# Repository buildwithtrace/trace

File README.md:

# Trace - AI-Native PCB Design Suite

**Trace is a modified version of the KiCad EDA software, enhanced with AI-native circuit design capabilities.**

> **Important:** Trace is based on [KiCad](https://www.kicad.org/), an open-source electronics design automation suite. This is an independent fork created and maintained by the Trace team. Trace is not affiliated with, endorsed by, or supported by the KiCad project or The Linux Foundation.

For specific documentation about [building Trace](https://docs.buildwithtrace.com/build/), policies and guidelines, and source code documentation see the [Trace Documentation](https://docs.buildwithtrace.com) website.

You may also take a look into the [Wiki](https://github.com/buildwithtrace/trace/wiki) and the [contribution guide](https://docs.buildwithtrace.com/contribute/).

---

## About Trace

Trace extends KiCad's powerful PCB design tools with:
- **AI Circuit Assistant**: Natural language circuit design and modification
- **Intelligent Component Search**: AI-native part finding and suggestions  
- **Automated Routing**: Smart trace routing with AI optimization
- **Cloud Integration**: Sync designs and collaborate with your team
- **Enhanced Workflow**: Streamlined UI for modern hardware engineering

## License & Compliance

### Open Source License

Trace is released under the **GNU General Public License v3** (GPLv3), the same license as KiCad.

- **License Text**: See [LICENSE](LICENSE) file in this repository
- **Source Code**: This repository contains the complete source code for Trace
- **Full Source Archive**: Available at https://github.com/buildwithtrace/trace

As required by GPLv3, you are free to:
- Use Trace for any purpose
- Study and modify the source code
- Share copies with others
- Distribute modified versions (under GPLv3)

### Copyright & Attribution

```
Copyright (C) 2025-2026 Trace Developers (see TRACE_AUTHORS.txt)
Copyright (C) 1992-2024 KiCad Developers (see AUTHORS.txt)

Trace incorporates substantial code from the KiCad project.
KiCad is copyright its contributors and licensed under GPLv3.
```

**Modification Notice**: This software is a modified version of KiCad EDA, adapted by the Trace team starting December 2025. Original KiCad code and modifications are both licensed under GPLv3.

### Trademark Notice

**KiCad** is a registered trademark of The Linux Foundation. All rights reserved.  
**Trace** is a trademark of the Trace team.

Trace is an independent product and is not affiliated with or endorsed by the KiCad project, The Linux Foundation, or any KiCad contributors. Any bugs, issues, or support requests for Trace should be directed to the Trace team, not the KiCad project.

### Third-Party Licenses

This software includes components under various open-source licenses:
- **KiCad Libraries**: Creative Commons Attribution-ShareAlike 4.0 (CC-BY-SA 4.0)
- **Various Components**: MIT, BSD, Apache, and other permissive licenses
- See individual `LICENSE*` files in subdirectories for details

### Proprietary Components

> **Important:** The [`trace/`](trace/) directory contains Trace's proprietary AI-native design modules and is **NOT** covered by GPLv3. All files under `trace/` and its subdirectories are **All Rights Reserved** and are provided for reference only. See [`trace/LICENSE`](trace/LICENSE) for the full terms. Contact hello@buildwithtrace.com for licensing inquiries.

### No Warranty

```
THIS SOFTWARE IS PROVIDED "AS IS" WITHOUT WARRANTY OF ANY KIND, EXPRESS OR
IMPLIED, INCLUDING BUT NOT LIMITED TO THE WARRANTIES OF MERCHANTABILITY,
FITNESS FOR A PARTICULAR PURPOSE AND NONINFRINGEMENT. IN NO EVENT SHALL THE
AUTHORS OR COPYRIGHT HOLDERS BE LIABLE FOR ANY CLAIM, DAMAGES OR OTHER
LIABILITY, WHETHER IN AN ACTION OF CONTRACT, TORT OR OTHERWISE, ARISING FROM,
OUT OF OR IN CONNECTION WITH THE SOFTWARE OR THE USE OR OTHER DEALINGS IN
THE SOFTWARE.
```

See the [LICENSE](LICENSE) file for complete GPL warranty disclaimer.

---

## Building Trace from Source

### Prerequisites

- **CMake** 3.16 or later
- **C++ compiler** with C++17 support (GCC 8+, Clang 8+, MSVC 2019+)
- **Python** 3.8+ with wxPython
- **Git** for cloning the repository
- Platform-specific dependencies (see below)

### Build Instructions

#### macOS

Use our official Mac builder:
```bash
git clone https://github.com/buildwithtrace/trace-mac-builder
cd trace-mac-builder
python build.py
```

See [trace-mac-builder](https://github.com/buildwithtrace/trace-mac-builder) for detailed instructions.

#### Windows

Use our official Windows builder:
```bash
git clone https://github.com/buildwithtrace/trace-win-builder
cd trace-win-builder
# Follow instructions in repository
```

See [trace-win-builder](https://github.com/buildwithtrace/trace-win-builder) for detailed instructions.

#### Linux

```bash
# Install dependencies (Ubuntu/Debian example)
sudo apt-get update
sudo apt-get install -y cmake g++ git python3 python3-wxgtk4.0 \
    libboost-all-dev libglew-dev libcairo2-dev libcurl4-openssl-dev \
    libssl-dev libngspice0-dev libocct-*-dev swig

# Clone and build
git clone https://github.com/buildwithtrace/trace
cd trace
mkdir -p build/release
cd build/release
cmake ../.. -DCMAKE_BUILD_TYPE=Release
make -j$(nproc)
sudo make install
```

For detailed build documentation, see [Developer Documentation](https://docs.buildwithtrace.com).

---

## Files

* [AUTHORS.txt](AUTHORS.txt) - KiCad authors, contributors, document writers and translators (see [original on GitLab](https://gitlab.com/kicad/code/kicad/-/blob/master/AUTHORS.txt))
* [TRACE_AUTHORS.txt](TRACE_AUTHORS.txt) - Trace-specific contributors and developers
* [CMakeLists.txt](CMakeLists.txt) - Main CMAKE build tool script
* [copyright.h](copyright.h) - A very short copy of the GNU General Public License to be included in new source files
* [Doxyfile](Doxyfile) - Doxygen config file for Trace
* [INSTALL.txt](INSTALL.txt) - The release (binary) installation instructions
* [uncrustify.cfg](uncrustify.cfg) - Uncrustify config file for uncrustify sources formatting tool
* [_clang-format](_clang-format) - clang config file for clang-format sources formatting tool

---

## Getting Started

1. **Download**: Get the latest Trace installer from [buildwithtrace.com](https://buildwithtrace.com)
2. **Install**: Run the installer for your platform
3. **Sign In**: Create a free account to access AI features
4. **Start Designing**: Launch Trace and start a new schematic

### AI Features

Trace's AI assistant helps you design circuits faster:
- Type what you want in natural language: "Add a 555 timer circuit"
- Ask questions: "How do I add decoupling capacitors?"
- Get component suggestions: "Find a low-power MCU for battery operation"
- Auto-route your PCB with intelligent algorithms

---

## Documentation

- **User Guide**: [docs.buildwithtrace.com/docs/guides/first-pcb](https://docs.buildwithtrace.com/guides/first-pcb)
- **API Documentation**: [docs.buildwithtrace.com/docs/api](https://docs.buildwithtrace.com/api/overview)
- **Discord Community**: [Join us on Discord](https://discord.gg/UNUvQxneCr) - Get help, report bugs, discuss features, and stay updated
- **KiCad Documentation**: For core EDA features, [KiCad docs](https://docs.kicad.org/) may be helpful

---

## Project Structure

- **[3d-viewer](3d-viewer)** - Sourcecode of the 3D viewer
- **[bitmap2component](bitmap2component)** - Sourcecode of the bitmap to PCB artwork converter
- **[cmake](cmake)** - Modules for the CMAKE build tool
- **[common](common)** - Sourcecode of the common library
- **[cvpcb](cvpcb)** - Sourcecode of the CvPCB tool
- **[demos](demos)** - Some demo examples
- **[doxygen](doxygen)** - Configuration for generating pretty doxygen manual of the codebase
- **[eeschema](eeschema)** - Sourcecode of the schematic editor with AI integration
- **[gerbview](gerbview)** - Sourcecode of the gerber viewer
- **[include](include)** - Interfaces to the common library
- **[kicad](kicad)** - Sourcecode of the project manager
- **[libs](libs)** - Sourcecode of Trace utilities (geometry and others)
- **[pagelayout_editor](pagelayout_editor)** - Sourcecode of the pagelayout editor
- **[patches](patches)** - Collection of patches for external dependencies
- **[pcbnew](pcbnew)** - Sourcecode of the printed circuit board editor
- **[plugins](plugins)** - Sourcecode for the 3D viewer plugins
- **[qa](qa)** - Unit testing framework for Trace
- **[resources](resources)** - Packaging resources such as bitmaps and operating system specific files
  - [bitmaps_png](resources/bitmaps_png) - Menu and program icons
  - [project_template](resources/project_template) - Project template
- **[scripting](scripting)** - Python integration for Trace
- **[thirdparty](thirdparty)** - Sourcecode of external libraries used in Trace but not written by the Trace team
- **[tools](tools)** - Helpers for developing, testing and building
- **[trace](trace)** - Trace-specific AI and integration code
- **[trace_assets](trace_assets)** - Trace branding and UI assets
- **[translation](translation)** - Translation data files
- **[utils](utils)** - Small utils for Trace, e.g. IDF, STEP, and OGL tools and converters

---

## Contributing

We welcome contributions! Trace is a fork of KiCad, and we maintain compatibility with KiCad file formats and architectural decisions. Developers familiar with KiCad will find the codebase familiar.

**Getting Started:**
- Join our [Discord community](https://discord.gg/UNUvQxneCr) - Primary hub for discussions, bug reports, questions, and announcements
- Check the [issue tracker](https://github.com/buildwithtrace/trace/issues) for "good first issue" labels
- For larger changes, discuss on Discord before starting work

**Important Notes:**
- All contributions must be compatible with GNU GPLv3
- By contributing, you agree to license your code under GPLv3
- Consider upstreaming useful improvements to [KiCad](https://gitlab.com/kicad/code/kicad) when applicable

See [CONTRIBUTING.md](CONTRIBUTING.md) for detailed guidelines on code style, pull requests, testing, and more.

---

## Support

- **Discord**: [Join our community](https://discord.gg/UNUvQxneCr) - Get help, report bugs, discuss features, ask questions
- **Website**: [buildwithtrace.com](https://buildwithtrace.com)
- **Email**: hello@buildwithtrace.com
- **Issues**: [GitHub Issues](https://github.com/buildwithtrace/trace/issues)

**Note**: For issues with core KiCad functionality (not Trace-specific features), consider also reporting to the [KiCad project](https://gitlab.com/kicad/code/kicad/-/issues) to benefit the wider community.

---

## Acknowledgments

Trace is built on the excellent work of the KiCad project and its contributors. We are grateful to the KiCad developers and the broader open-source EDA community for creating a solid foundation.

**KiCad Contributors**: See [AUTHORS.txt](AUTHORS.txt) for the full list of KiCad contributors whose work is included in Trace. The original list is maintained at [gitlab.com/kicad/code/kicad](https://gitlab.com/kicad/code/kicad/-/blob/master/AUTHORS.txt).

**Trace Contributors**: See [TRACE_AUTHORS.txt](TRACE_AUTHORS.txt) for Trace-specific contributors. Copyright (C) 2025-2026 Trace Developers.

---

## Repository Information

- **Main Repository**: https://github.com/buildwithtrace/trace
- **Mac Builder**: https://github.com/buildwithtrace/trace-mac-builder
- **Windows Builder**: https://github.com/buildwithtrace/trace-win-builder
- **Backend API**: (Proprietary - not included in this repository)

---

**Version**: 1.0.0  
**Based on**: KiCad EDA  
**Modified**: January 2026  
**License**: GNU GPLv3

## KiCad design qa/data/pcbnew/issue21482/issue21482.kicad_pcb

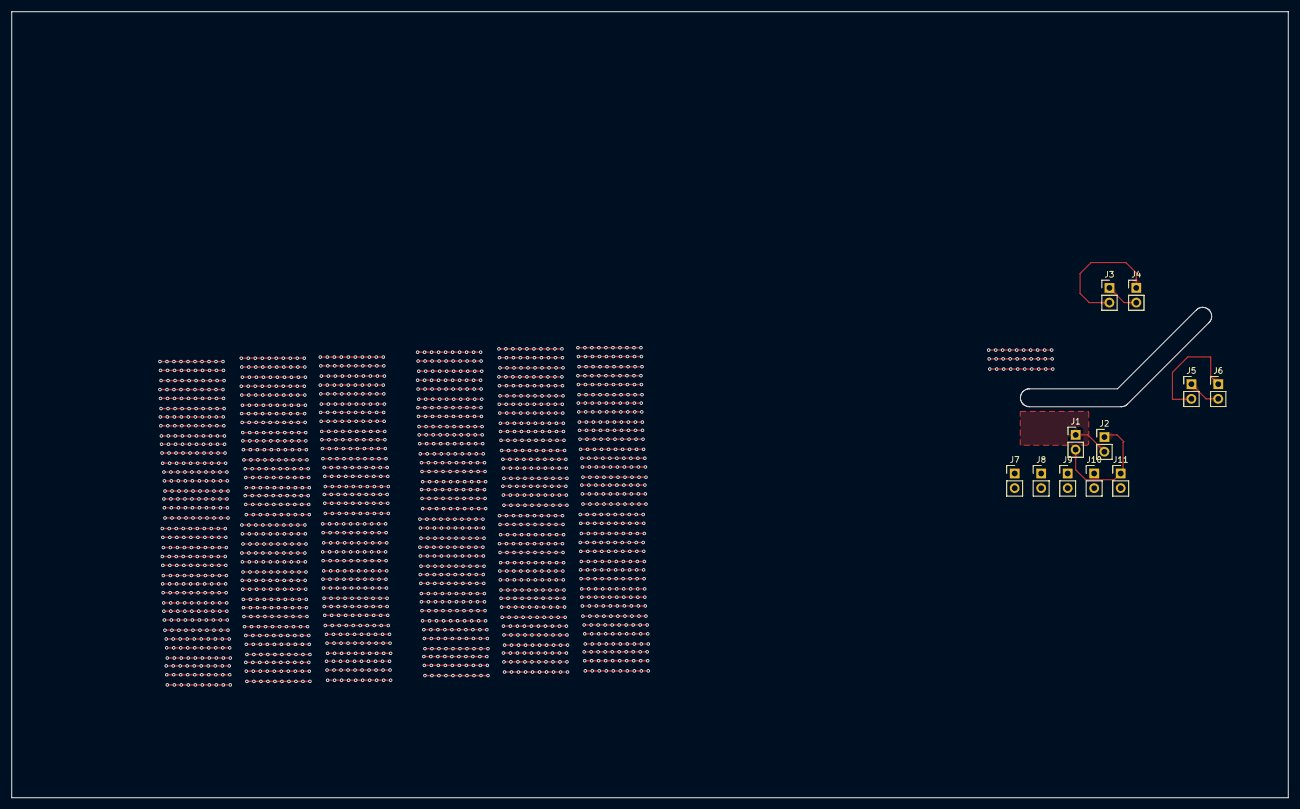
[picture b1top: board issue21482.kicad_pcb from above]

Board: 8 copper layers, 221.1 x 136.1 mm, 11 parts (0 on the bottom side), 6 nets.

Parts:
J1, J2, J3, J4, J5, J6, J7, J8, J9, J10, J11: Conn_01x02_Pin; PinHeader_1x02_P2.54mm_Vertical

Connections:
unnamed: J1.1, J2.2
unnamed: J1.2, J2.1
unnamed: J3.1, J4.2
unnamed: J3.2, J4.1
unnamed: J5.1, J6.2
unnamed: J5.2, J6.1

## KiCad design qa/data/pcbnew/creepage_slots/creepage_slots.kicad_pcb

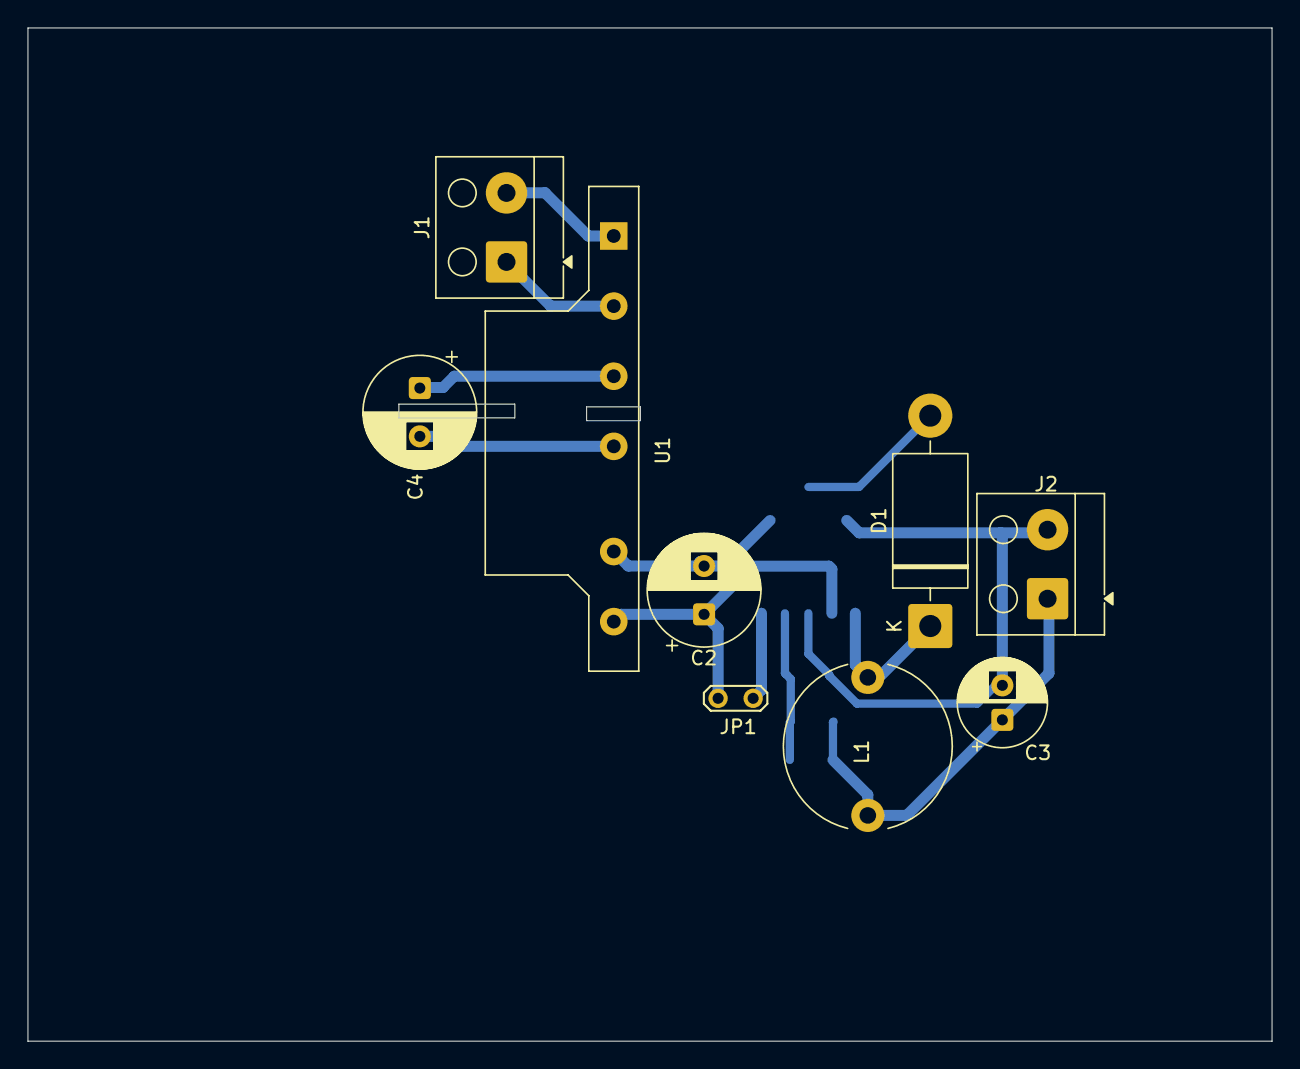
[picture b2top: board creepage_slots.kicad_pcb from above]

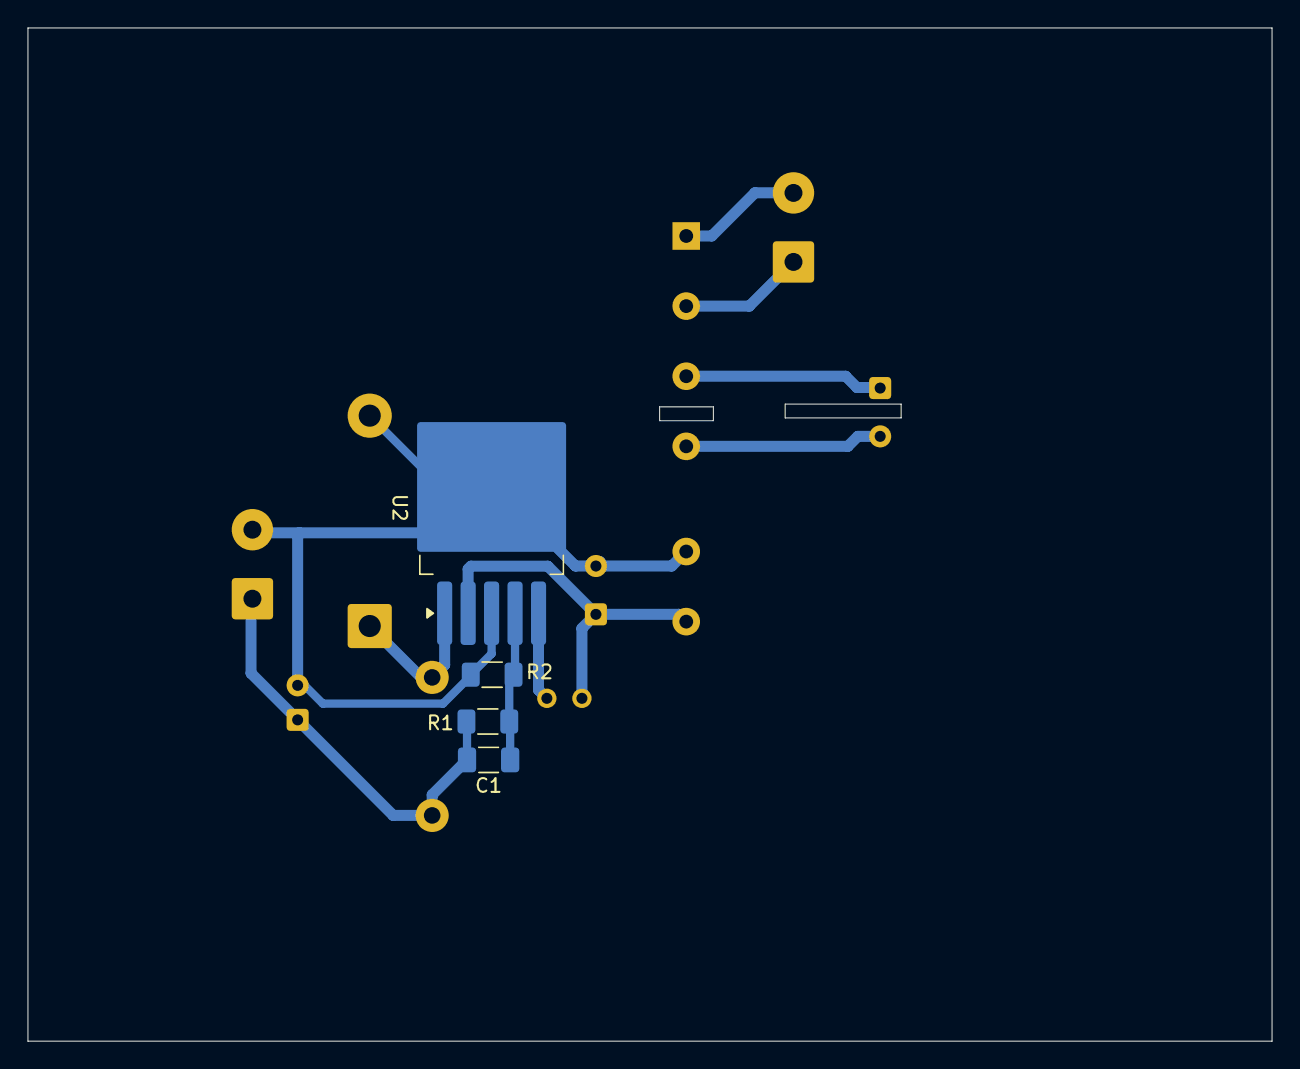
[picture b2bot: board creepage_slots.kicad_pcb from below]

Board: 2 copper layers, 90.1 x 73.4 mm, 13 parts (4 on the bottom side), 10 nets.

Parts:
C1: 6n8; C_1206_3216Metric_Pad1.33x1.80mm_HandSolder
C2: 100u/35V; CP_Radial_D8.0mm_P3.50mm
C3: 330u/6,3V; CP_Radial_D6.3mm_P2.50mm
C4: 10u/350V; CP_Radial_D8.0mm_P3.50mm
D1: 1N5822; D_DO-201AD_P15.24mm_Horizontal
J1: Vstup 230V; Altech_AK100_1x02_P5.00mm
J2: Vystup +1,8V; Altech_AK100_1x02_P5.00mm
JP1: Jumper_2_Bridged; TestPoint_2Pads_Pitch2.54mm_Drill0.8mm
L1: 150uH; L_Radial_D12.0mm_P10.00mm_Neosid_SD12_style1
R1: 470R; R_1206_3216Metric_Pad1.30x1.75mm_HandSolder
R2: 1k; R_1206_3216Metric_Pad1.30x1.75mm_HandSolder
U1: PBO-3-S24; Converter_ACDC_CUI_PBO-3-Sxx_THT_Vertical
U2: LM2595S-ADJ; TO-263-5_TabPin3

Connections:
+1V8: C1.2, C3.1, J2.1, L1.2, R1.1
GND: C2.2, C3.2, D1.2 (A), J2.2, R2.1, U1.10 (-Vo), U2.3 (GND)
unnamed: D1.1 (K), L1.1, U2.1 (OUT)
unnamed: J1.1, U1.3 (AC(L))
unnamed: J1.2, U1.1 (AC(N))
unnamed: JP1.1 (A), U2.5 (ON/~OFF)
unnamed: C2.1, JP1.2 (B), U1.12 (+Vo), U2.2 (VIN)
unnamed: C4.1, U1.5 (+V(CAP))
unnamed: C4.2, U1.7 (-V(CAP))
unnamed: C1.1, R1.2, R2.2, U2.4 (FB)

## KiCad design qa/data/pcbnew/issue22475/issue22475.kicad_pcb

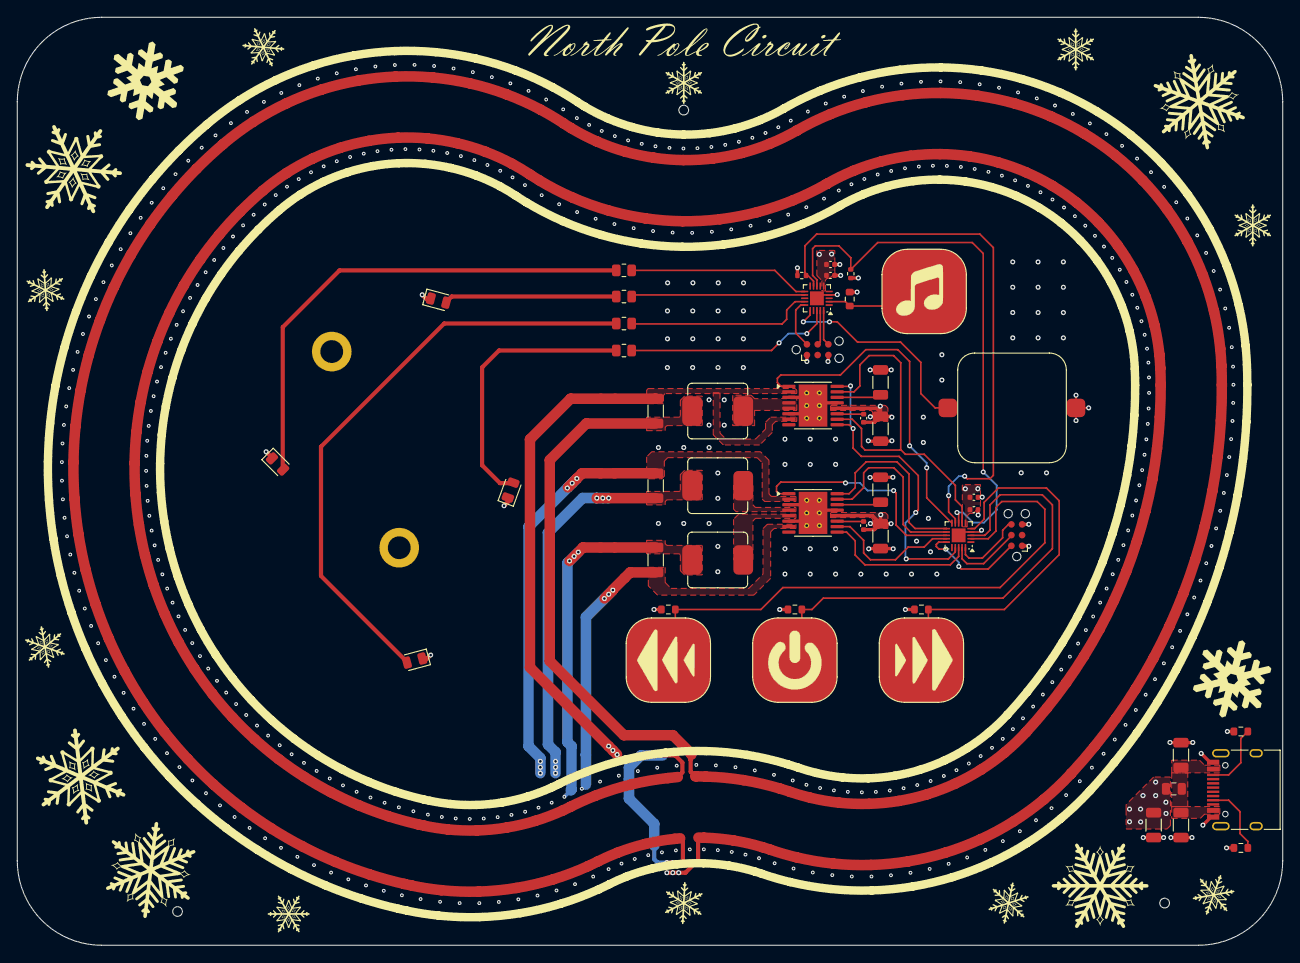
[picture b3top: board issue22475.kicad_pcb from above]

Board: 4 copper layers, 150.0 x 110.0 mm, 56 parts (0 on the bottom side), 47 nets.

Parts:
BZ1: FUET-1325H; FUET-1325
C1, C2, C3, C4, C7, C8, C11, C12: 10uF; C_1206_3216Metric
C5, C9: 2.2uF; C_1206_3216Metric
C6, C10: 10nF; C_0402_1005Metric
C13, C14, C15, C16: 100n; C_0402_1005Metric
D1, D2, D3, D4: LED; LED_0805_2012Metric
F1: 500mA; Fuse_0805_2012Metric
H5, H6: M2.5; MountingHole_2.7mm_M2.5_DIN965_Pad
H7, H8, H9: Tooling; tooling_hole
J1: USB_C_Receptacle_USB2.0_16P; USB_C_Receptacle_HRO_TYPE-C-31-M-12
J2, J3: PROG; Tag-Connect_TC2030-IDC-NL_2x03_P1.27mm_Vertical
L1, L2, L3: SMMS0650-101M
NT1: PWM_G; NetTie_1.25mm
NT2: PWM_A; NetTie_1.25mm
NT3: PWM_B; NetTie_1.25mm
R1, R2: 5k1; R_0603_1608Metric
R3, R4, R5, R6: 180R; R_0805_2012Metric
R7, R8, R9, R10: 510k; R_0603_1608Metric
R11, R12: 3.3k; R_0402_1005Metric
TP3: SPD-; Cap_Touch_10mm
TP4: RUN; Cap_Touch_10mm
TP5: SPD+; Cap_Touch_10mm
TP6: MUSIC; Cap_Touch_10mm
U1, U2: DRV8833PWP; HTSSOP-16-1EP_4.4x5mm_P0.65mm_EP3.4x5mm_Mask2.46x2.31mm_The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
U3, U4: CH32V003FxUx; QFN-20-1EP_3x3mm_P0.4mm_EP1.65x1.65mm

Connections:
+5V: C3.1, C4.1, C6.1, C8.1, C10.1, C13.1, C14.1, C15.1, C16.1, F1.2, J2.1 (VCC), J3.1 (VCC), R7.1, R8.1, R9.1, R10.1, R11.1, R12.1, U1.12 (VM), U2.12 (VM), U3.6 (VDD), U4.6 (VDD)
/A1_OUT: C11.1, NT2.2, U2.2 (AOUT1)
/A2_OUT: C11.2, L2.2, NT2.1
/B1_OUT: C12.1, NT3.2, U2.7 (BOUT1)
/B2_OUT: C12.2, L3.2, NT3.1
/BUZZ: BZ1.1 (+), U4.16 (PD2)
/CC1: J1.A5 (CC1), R1.1
/CC2: J1.B5 (CC2), R2.1
/G1_OUT: C7.1, NT1.2, U1.2 (AOUT1), U1.7 (BOUT1)
/G2_OUT: C7.2, L1.2, NT1.1
/LED1: R5.1, U4.11 (PC4)
/LED2: R4.1, U4.12 (PC5)
/LED3: R3.1, U4.14 (PC7)
/LED4: R6.1, U4.18 (PD4)
/MUSIC: R10.2, TP6.1, U4.2 (PA1)
/PWM_A1: U2.16 (AIN1), U3.11 (PC4)
/PWM_A2: U2.15 (AIN2), U3.12 (PC5)
/PWM_B1: U2.9 (BIN1), U3.18 (PD4)
/PWM_B2: U2.10 (BIN2), U3.14 (PC7)
/PWM_G1: U1.9 (BIN1), U1.16 (AIN1), U3.17 (PD3)
/PWM_G2: U1.10 (BIN2), U1.15 (AIN2), U3.7 (PC0)
/RUN: R8.2, TP4.1, U3.3 (PA2)
/RX0: J2.4 (SWCLK), U3.19 (PD5)
/RX1: J3.4 (SWCLK), U4.19 (PD5)
/SCL: R12.2, U3.9 (PC2), U4.9 (PC2)
/SDA: R11.2, U3.8 (PC1), U4.8 (PC1)
/SLEEP_G: U1.1 (~SLEEP), U3.10 (PC3)
/SLEEP_PH: U2.1 (~SLEEP), U3.13 (PC6)
/SPD++: R9.2, TP5.1, U3.5 (PD0)
/SPD--: R7.2, TP3.1, U3.2 (PA1)
/SWDIO0: J2.2 (SWDIO), U3.15 (PD1)
/SWDIO1: J3.2 (SWDIO), U4.15 (PD1)
/TX0: J2.6 (SWO), U3.20 (PD6)
/TX1: J3.6 (SWO), U4.20 (PD6)
GND: BZ1.2 (-), C1.2, C2.2, C3.2, C4.2, C5.1, C8.2, C9.1, C13.2, C14.2, C15.2, C16.2, D1.1 (K), D2.1 (K), D3.1 (K), D4.1 (K), J1.A1 (GND), J1.A12 (GND), J1.B1 (GND), J1.B12 (GND), J1.S1 (SHIELD), J2.5 (GND), J3.5 (GND), R1.2, R2.2, U1.3 (AISEN), U1.6 (BISEN), U1.13 (GND), U1.17 (GND), U2.3 (AISEN), U2.6 (BISEN), U2.13 (GND), U2.17 (GND), U3.4 (VSS), U3.21 (VSS), U4.4 (VSS), U4.21 (VSS)
unnamed: D1.2 (A), R3.2
unnamed: D2.2 (A), R4.2
unnamed: D3.2 (A), R5.2
unnamed: D4.2 (A), R6.2
unnamed: L1.1, U1.4 (AOUT2), U1.5 (BOUT2)
unnamed: C6.2, U1.11 (VCP)
unnamed: C5.2, U1.14 (VINT)
unnamed: L2.1, U2.4 (AOUT2)
unnamed: L3.1, U2.5 (BOUT2)
unnamed: C10.2, U2.11 (VCP)
unnamed: C9.2, U2.14 (VINT)
VDD: C1.1, C2.1, F1.1, J1.A4 (VBUS), J1.A9 (VBUS), J1.B4 (VBUS), J1.B9 (VBUS)

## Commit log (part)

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2026-03-04 Release 1.1.0
    Trace 1.1.0 release. AI chat integration, Trace branding, and various improvements.
    Made-with: Cursor
2026-03-07 Release 1.2.0
    Trace now supports KiCAD 10, some bug fixes and new features
    ## New Features
    - Trace now supports KiCAD 10
    ## Bug Fixes
    - Fixed the app suddenly stopping during stream
    ## Improvements
2026-03-08 docs: fix broken trace-mac-builder links in README
    Remove references to trace-mac-builder repository which does not exist.
    Direct macOS users to Developer Documentation instead.
    Remove Mac Builder from Repository Information section.
    Made-with: Cursor
2026-05-11 Release 1.3.1
    Team collaboration and project management
    ## New Features
    - Team collaboration and project management
